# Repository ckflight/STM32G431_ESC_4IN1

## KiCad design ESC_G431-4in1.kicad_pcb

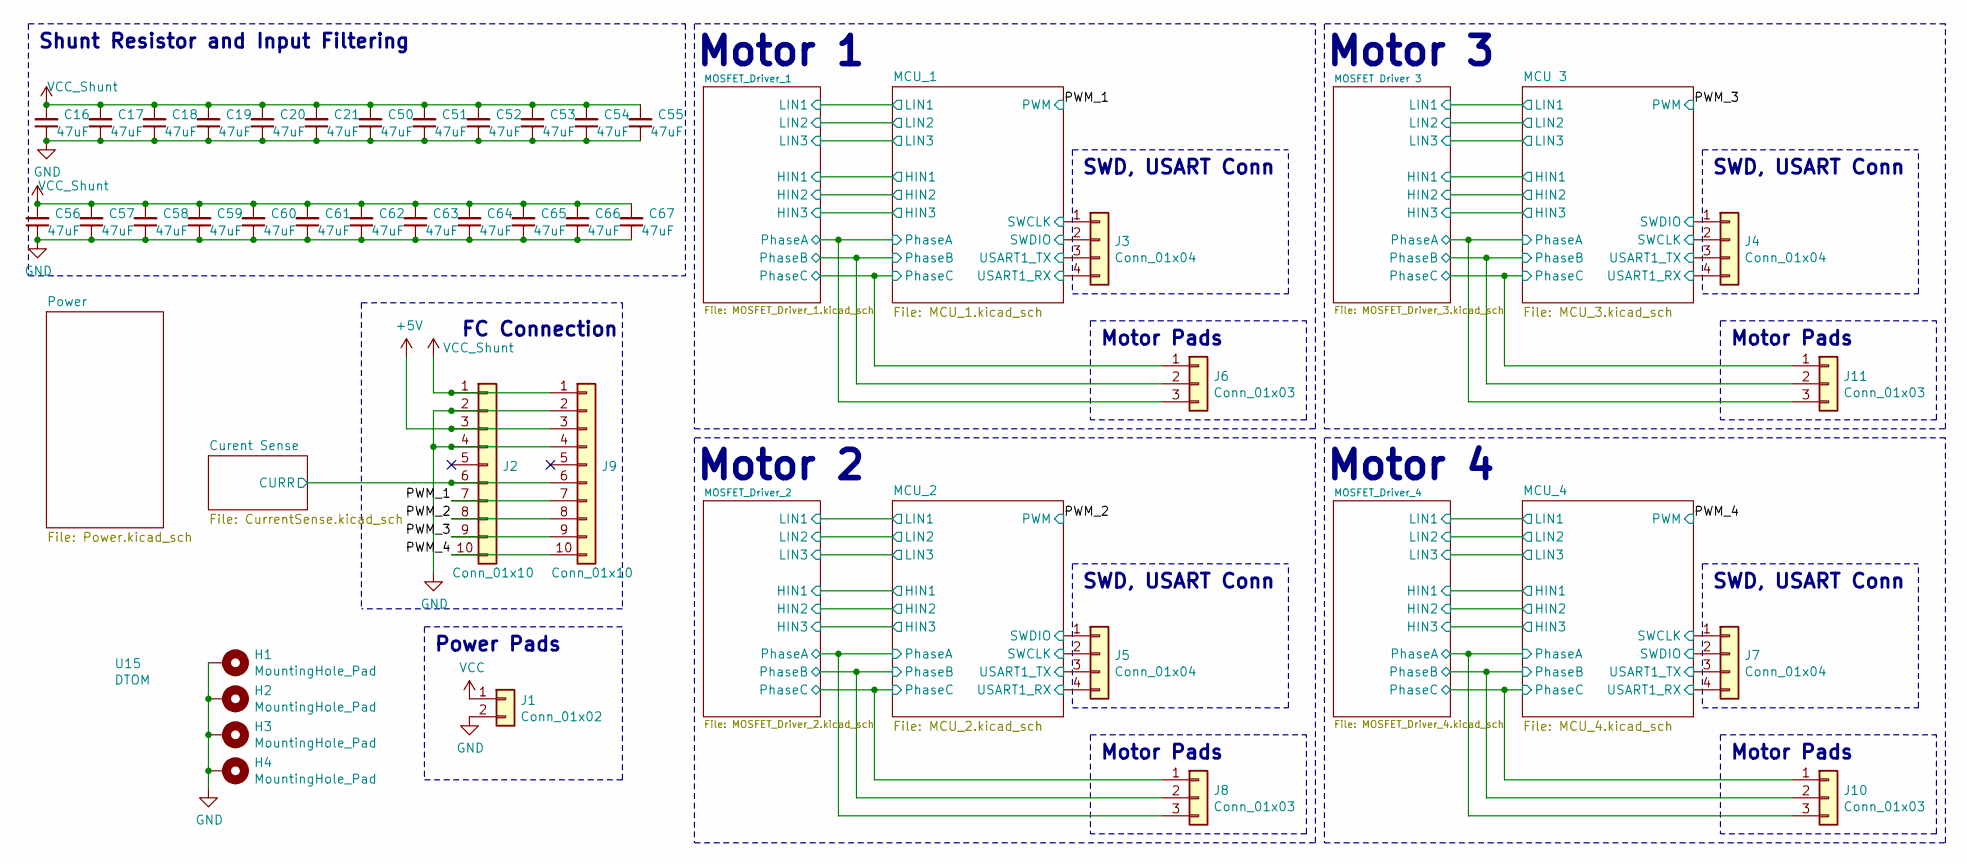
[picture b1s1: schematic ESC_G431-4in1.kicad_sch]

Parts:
C16, C17, C18, C19, C20, C21, C50, C51, C52, C53, C54, C55, C56, C57, C58, C59, C60, C61, C62, C63, C64, C65, C66, C67: 47uF; C_1206_3216Metric
H1, H2, H3, H4: MountingHole_Pad; MountingHole_4in1ESC
J1: Conn_01x02; Conn_PowerPad_4in1
J2: Conn_01x10; JST_SH_SM10B-SRSS-TB_1x10-1MP_P1.00mm_Horizontal
J3, J4, J5, J7: Conn_01x04; Conn_Debug
J6, J8, J10, J11: Conn_01x03; Conn_MotorPhase
J9: Conn_01x10; Conn_FC_Solder_10
U15: DTOM; DTOM_L

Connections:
+5V: J2.3, J9.3; also elsewhere on the board
/Curent Sense/CURR: J2.6, J9.6; also elsewhere on the board
/MCU 3/PhaseA: J11.3; also elsewhere on the board
/MCU 3/PhaseB: J11.2; also elsewhere on the board
/MCU 3/PhaseC: J11.1; also elsewhere on the board
/MCU 3/SWCLK: J4.2; also elsewhere on the board
/MCU 3/SWDIO: J4.1; also elsewhere on the board
/MCU 3/USART1_RX: J4.4; also elsewhere on the board
/MCU 3/USART1_TX: J4.3; also elsewhere on the board
/MCU_1/PhaseA: J6.3; also elsewhere on the board
/MCU_1/PhaseB: J6.2; also elsewhere on the board
/MCU_1/PhaseC: J6.1; also elsewhere on the board
/MCU_1/SWCLK: J3.1; also elsewhere on the board
/MCU_1/SWDIO: J3.2; also elsewhere on the board
/MCU_1/USART1_RX: J3.4; also elsewhere on the board
/MCU_1/USART1_TX: J3.3; also elsewhere on the board
/MCU_2/PhaseA: J8.3; also elsewhere on the board
/MCU_2/PhaseB: J8.2; also elsewhere on the board
/MCU_2/PhaseC: J8.1; also elsewhere on the board
/MCU_2/SWCLK: J5.2; also elsewhere on the board
/MCU_2/SWDIO: J5.1; also elsewhere on the board
/MCU_2/USART1_RX: J5.4; also elsewhere on the board
/MCU_2/USART1_TX: J5.3; also elsewhere on the board
/MCU_4/PhaseA: J10.3; also elsewhere on the board
/MCU_4/PhaseB: J10.2; also elsewhere on the board
/MCU_4/PhaseC: J10.1; also elsewhere on the board
/MCU_4/SWCLK: J7.1; also elsewhere on the board
/MCU_4/SWDIO: J7.2; also elsewhere on the board
/MCU_4/USART1_RX: J7.4; also elsewhere on the board
/MCU_4/USART1_TX: J7.3; also elsewhere on the board
/PWM_1: J2.7, J9.7; also elsewhere on the board
/PWM_2: J2.8, J9.8; also elsewhere on the board
/PWM_3: J2.9, J9.9; also elsewhere on the board
/PWM_4: J2.10, J9.10; also elsewhere on the board
GND: C16.1, C17.1, C18.1, C19.1, C20.1, C21.1, C50.1, C51.1, C52.1, C53.1, C54.1, C55.1, C56.1, C57.1, C58.1, C59.1, C60.1, C61.1, C62.1, C63.1, C64.1, C65.1, C66.1, C67.1, H1.1, H2.1, H3.1, H4.1, J1.2, J2.2, J2.4, J9.2, J9.4; also elsewhere on the board
VCC: J1.1; also elsewhere on the board
VCC_Shunt: C16.2, C17.2, C18.2, C19.2, C20.2, C21.2, C50.2, C51.2, C52.2, C53.2, C54.2, C55.2, C56.2, C57.2, C58.2, C59.2, C60.2, C61.2, C62.2, C63.2, C64.2, C65.2, C66.2, C67.2, J2.1, J9.1; also elsewhere on the board

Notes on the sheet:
SWD, USART Conn
Motor Pads
Motor 2
Motor 4
Motor 1
Motor 3
FC Connection
Shunt Resistor and Input Filtering
Power Pads

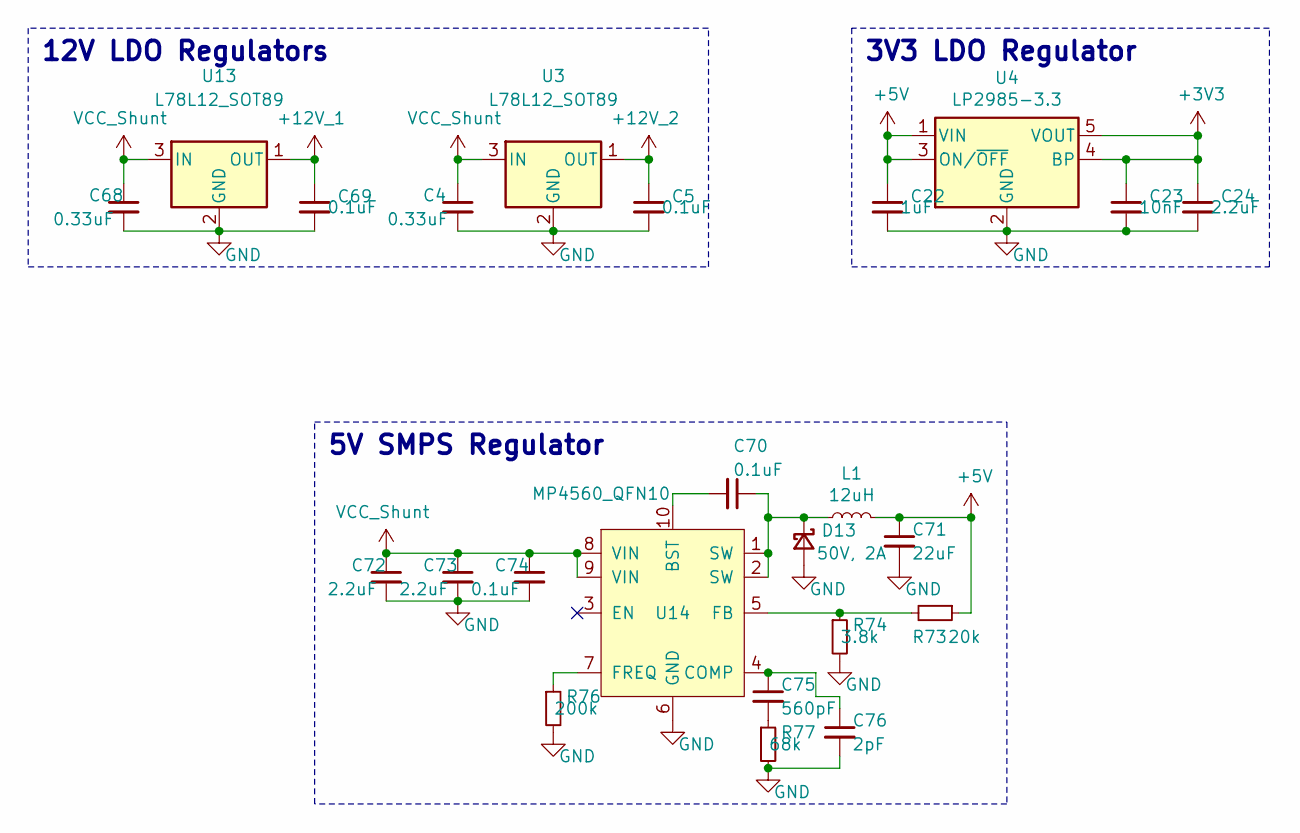
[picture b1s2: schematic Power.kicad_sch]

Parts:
C4, C68: 0.33uF; C_0603_1608Metric
C5, C69: 0.1uF; C_0603_1608Metric
C22: 1uF; C_0402_1005Metric
C23: 10nF; C_0402_1005Metric
C24, C72, C73: 2.2uF; C_0603_1608Metric
C70, C74: 0.1uF; C_0402_1005Metric
C71: 22uF; C_0603_1608Metric
C75: 560pF; C_0402_1005Metric
C76: 2pF; C_0402_1005Metric
D13: 50V, 2A; D_SOD-123F
L1: 12uH; L_XGL4030
R73: 20k; R_0402_1005Metric
R74: 3.8k; R_0402_1005Metric
R76: 200k; R_0402_1005Metric
R77: 68k; R_0402_1005Metric
U3, U13: L78L12_SOT89; L78L12ACUTR
U4: LP2985-3.3; SOT-23-5
U14: MP4560_QFN10; DFN-10-1EP_3x3mm_P0.5mm_EP1.7x2.5mm

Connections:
+3V3: C23.1, C24.1, U4.4 (BP), U4.5 (VOUT); also elsewhere on the board
+5V: C22.1, C71.1, L1.2, R73.1, U4.1 (VIN), U4.3 (ON/~OFF); also elsewhere on the board
+12V_1: C69.1, U13.1 (OUT); also elsewhere on the board
+12V_2: C5.1, U3.1 (OUT); also elsewhere on the board
GND: C4.2, C5.2, C22.2, C23.2, C24.2, C68.2, C69.2, C71.2, C72.2, C73.2, C74.2, C76.2, D13.2 (A), R74.2, R76.2, R77.2, U3.2 (GND), U4.2 (GND), U13.2 (GND), U14.6 (GND); also elsewhere on the board
unnamed: C70.1, D13.1 (K), L1.1, U14.1 (SW), U14.2 (SW)
unnamed: C70.2, U14.10 (BST)
unnamed: C75.1, C76.1, U14.4 (COMP)
unnamed: C75.2, R77.1
unnamed: R73.2, R74.1, U14.5 (FB)
unnamed: R76.1, U14.7 (FREQ)
VCC_Shunt: C4.1, C68.1, C72.1, C73.1, C74.1, U3.3 (IN), U13.3 (IN), U14.8 (VIN), U14.9 (VIN); also elsewhere on the board

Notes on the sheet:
12V LDO Regulators
3V3 LDO Regulator
5V SMPS Regulator

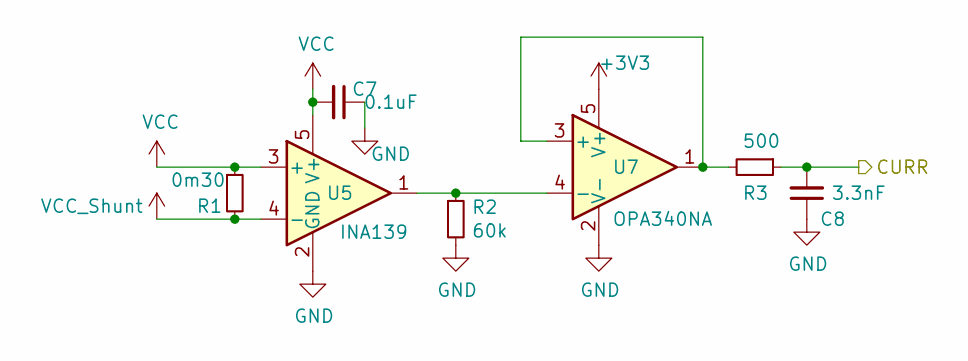
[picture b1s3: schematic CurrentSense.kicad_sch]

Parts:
C7: 0.1uF; C_0402_1005Metric
C8: 3.3nF; C_0402_1005Metric
R1: 0m30; R_Shunt_Vishay_WSLP2726
R2: 60k; R_0402_1005Metric
R3: 500; R_0402_1005Metric
U5: INA139; SOT-23-5
U7: OPA340NA; SOT-23-5

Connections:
+3V3: U7.5 (V+); also elsewhere on the board
/Curent Sense/CURR: C8.2, R3.1; also elsewhere on the board
GND: C7.1, C8.1, R2.2, U5.2 (GND), U7.2 (V-); also elsewhere on the board
unnamed: R2.1, U5.1, U7.4 (-)
unnamed: R3.2, U7.1, U7.3 (+)
VCC: C7.2, R1.1, U5.3 (+), U5.5 (V+); also elsewhere on the board
VCC_Shunt: R1.2, U5.4 (-); also elsewhere on the board

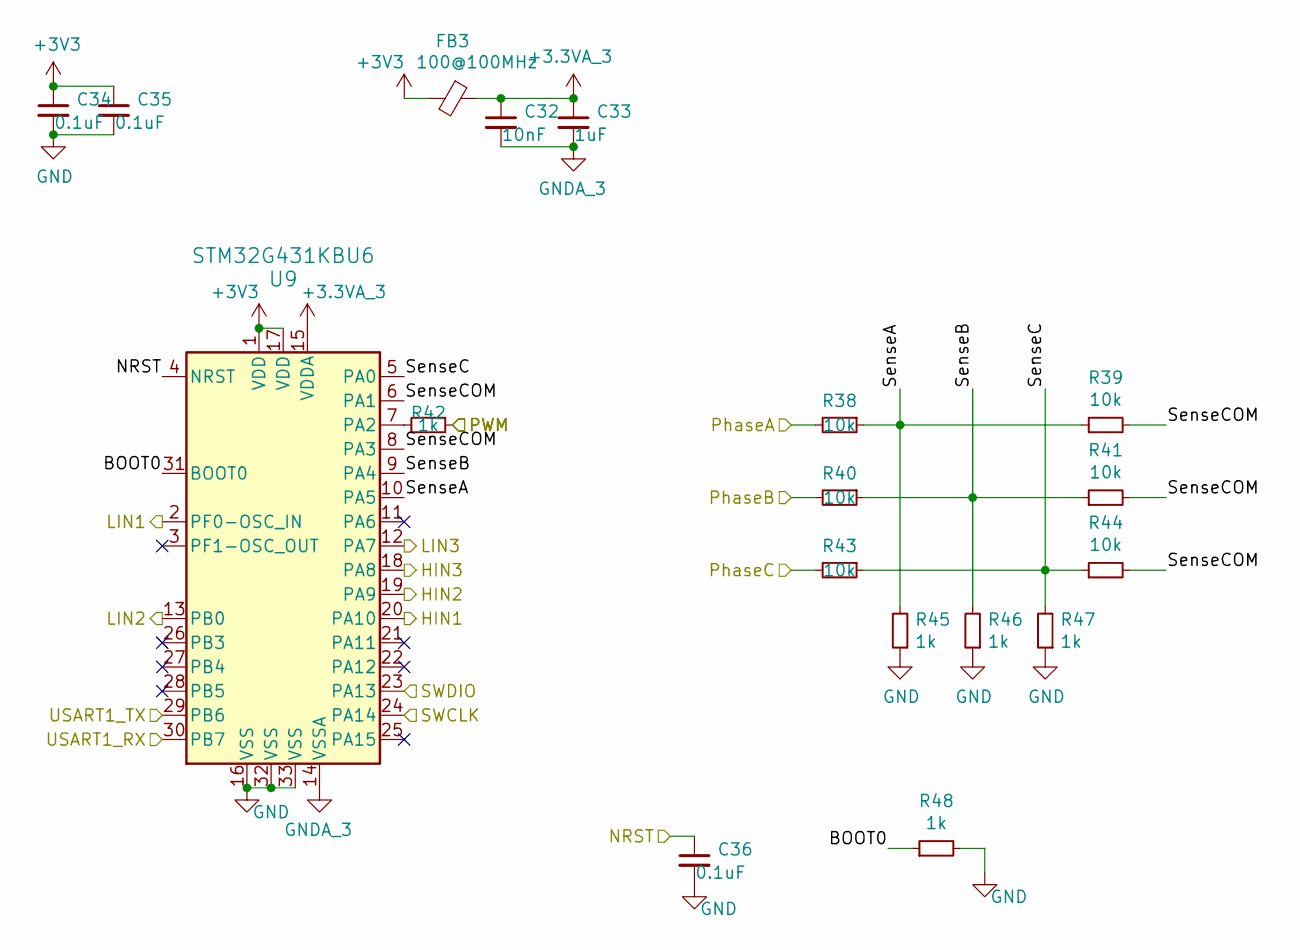
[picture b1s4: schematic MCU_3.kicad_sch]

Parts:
C32: 10nF; C_0402_1005Metric
C33: 1uF; C_0402_1005Metric
C34, C35, C36: 0.1uF; C_0402_1005Metric
FB3: 100@100MHz; L_0603_1608Metric
R38, R39, R40, R41, R43, R44: 10k; R_0402_1005Metric
R42, R45, R46, R47, R48: 1k; R_0402_1005Metric
U9: STM32G431KBU6; QFN-32-1EP_5x5mm_P0.5mm_EP3.45x3.45mm_STM32

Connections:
+3.3VA_3: C32.1, C33.1, FB3.1, U9.15 (VDDA)
+3V3: C34.1, C35.1, FB3.2, U9.1 (VDD), U9.17 (VDD); also elsewhere on the board
/MCU 3/BOOT0: R48.1, U9.31 (BOOT0)
/MCU 3/HIN1: U9.20 (PA10); also elsewhere on the board
/MCU 3/HIN2: U9.19 (PA9); also elsewhere on the board
/MCU 3/HIN3: U9.18 (PA8); also elsewhere on the board
/MCU 3/LIN1: U9.2 (PF0-OSC_IN); also elsewhere on the board
/MCU 3/LIN2: U9.13 (PB0); also elsewhere on the board
/MCU 3/LIN3: U9.12 (PA7); also elsewhere on the board
/MCU 3/NRST: C36.1, U9.4 (NRST)
/MCU 3/PhaseA: R38.2; also elsewhere on the board
/MCU 3/PhaseB: R40.2; also elsewhere on the board
/MCU 3/PhaseC: R43.2; also elsewhere on the board
/MCU 3/SWCLK: U9.24 (PA14); also elsewhere on the board
/MCU 3/SWDIO: U9.23 (PA13); also elsewhere on the board
/MCU 3/SenseA: R38.1, R39.1, R45.2, U9.10 (PA5)
/MCU 3/SenseB: R40.1, R41.1, R46.2, U9.9 (PA4)
/MCU 3/SenseC: R43.1, R44.1, R47.2, U9.5 (PA0)
/MCU 3/SenseCOM: R39.2, R41.2, R44.2, U9.6 (PA1), U9.8 (PA3)
/MCU 3/USART1_RX: U9.30 (PB7); also elsewhere on the board
/MCU 3/USART1_TX: U9.29 (PB6); also elsewhere on the board
/PWM_3: R42.2; also elsewhere on the board
GND: C34.2, C35.2, C36.2, R45.1, R46.1, R47.1, R48.2, U9.16 (VSS), U9.32 (VSS), U9.33 (VSS); also elsewhere on the board
GNDA_3: C32.2, C33.2, U9.14 (VSSA)
unnamed: R42.1, U9.7 (PA2)

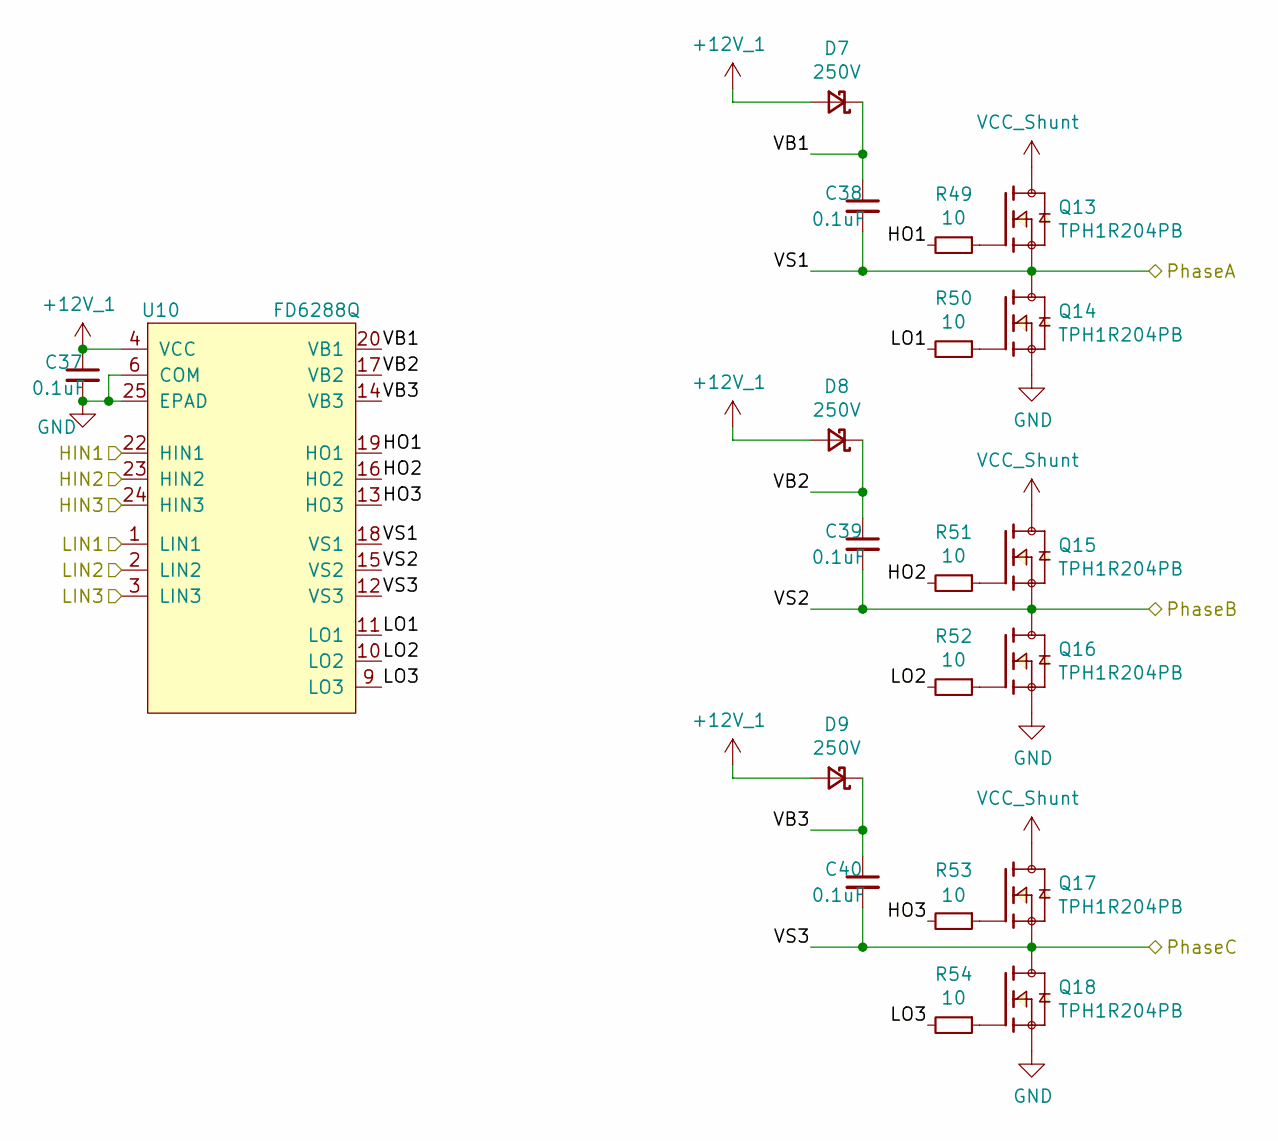
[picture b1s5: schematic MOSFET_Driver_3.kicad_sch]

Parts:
C37: 0.1uF; C_0402_1005Metric
C38, C39, C40: 0.1uF; C_0603_1608Metric
D7, D8, D9: 250V; D_SOD-523
Q13, Q14, Q15, Q16, Q17, Q18: TPH1R204PB; PARTREV 3
R49, R50, R51, R52, R53, R54: 10; R_0402_1005Metric
U10: FD6288Q; QFN-24-1EP_4x4mm_P0.5mm_EP2.7x2.7mm

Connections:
+12V_1: C37.1, D7.2 (A), D8.2 (A), D9.2 (A), U10.4 (VCC); also elsewhere on the board
/MCU 3/HIN1: U10.22 (HIN1); also elsewhere on the board
/MCU 3/HIN2: U10.23 (HIN2); also elsewhere on the board
/MCU 3/HIN3: U10.24 (HIN3); also elsewhere on the board
/MCU 3/LIN1: U10.1 (LIN1); also elsewhere on the board
/MCU 3/LIN2: U10.2 (LIN2); also elsewhere on the board
/MCU 3/LIN3: U10.3 (LIN3); also elsewhere on the board
/MCU 3/PhaseA: C38.2, Q13.1, Q13.2, Q13.3, Q14.5, Q14.6, Q14.7, Q14.8, Q14.9, U10.18 (VS1); also elsewhere on the board
/MCU 3/PhaseB: C39.2, Q15.1, Q15.2, Q15.3, Q16.5, Q16.6, Q16.7, Q16.8, Q16.9, U10.15 (VS2); also elsewhere on the board
/MCU 3/PhaseC: C40.2, Q17.1, Q17.2, Q17.3, Q18.5, Q18.6, Q18.7, Q18.8, Q18.9, U10.12 (VS3); also elsewhere on the board
/MOSFET Driver 3/HO1: R49.2, U10.19 (HO1)
/MOSFET Driver 3/HO2: R51.2, U10.16 (HO2)
/MOSFET Driver 3/HO3: R53.2, U10.13 (HO3)
/MOSFET Driver 3/LO1: R50.2, U10.11 (LO1)
/MOSFET Driver 3/LO2: R52.2, U10.10 (LO2)
/MOSFET Driver 3/LO3: R54.2, U10.9 (LO3)
/MOSFET Driver 3/VB1: C38.1, D7.1 (K), U10.20 (VB1)
/MOSFET Driver 3/VB2: C39.1, D8.1 (K), U10.17 (VB2)
/MOSFET Driver 3/VB3: C40.1, D9.1 (K), U10.14 (VB3)
GND: C37.2, Q14.1, Q14.2, Q14.3, Q16.1, Q16.2, Q16.3, Q18.1, Q18.2, Q18.3, U10.6 (COM), U10.25 (EPAD); also elsewhere on the board
unnamed: Q13.4, R49.1
unnamed: Q14.4, R50.1
unnamed: Q15.4, R51.1
unnamed: Q16.4, R52.1
unnamed: Q17.4, R53.1
unnamed: Q18.4, R54.1
VCC_Shunt: Q13.5, Q13.6, Q13.7, Q13.8, Q13.9, Q15.5, Q15.6, Q15.7, Q15.8, Q15.9, Q17.5, Q17.6, Q17.7, Q17.8, Q17.9; also elsewhere on the board

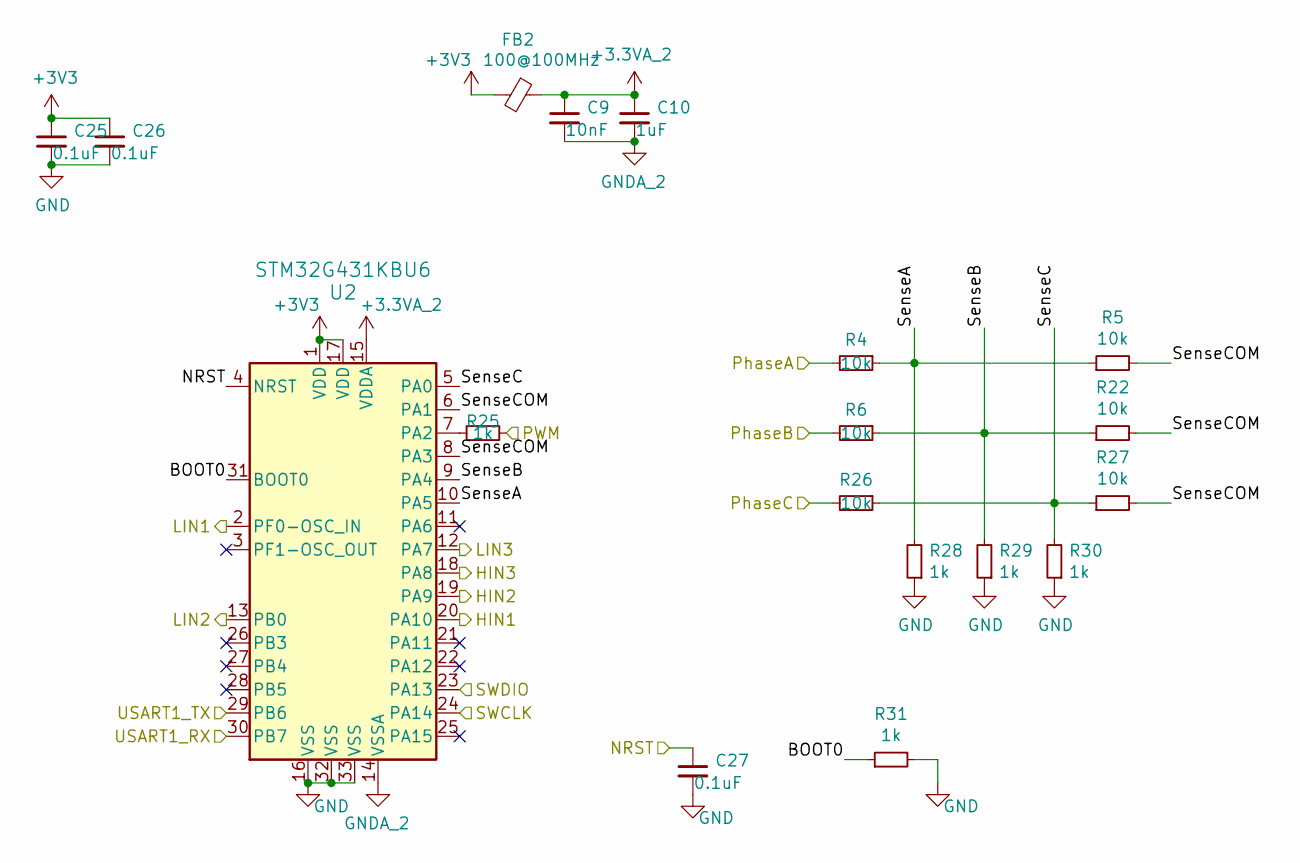
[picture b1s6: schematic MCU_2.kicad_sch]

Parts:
C9: 10nF; C_0402_1005Metric
C10: 1uF; C_0402_1005Metric
C25, C26, C27: 0.1uF; C_0402_1005Metric
FB2: 100@100MHz; L_0603_1608Metric
R4, R5, R6, R22, R26, R27: 10k; R_0402_1005Metric
R25, R28, R29, R30, R31: 1k; R_0402_1005Metric
U2: STM32G431KBU6; QFN-32-1EP_5x5mm_P0.5mm_EP3.45x3.45mm_STM32

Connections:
+3.3VA_2: C9.1, C10.1, FB2.1, U2.15 (VDDA)
+3V3: C25.1, C26.1, FB2.2, U2.1 (VDD), U2.17 (VDD); also elsewhere on the board
/MCU_2/BOOT0: R31.1, U2.31 (BOOT0)
/MCU_2/HIN1: U2.20 (PA10); also elsewhere on the board
/MCU_2/HIN2: U2.19 (PA9); also elsewhere on the board
/MCU_2/HIN3: U2.18 (PA8); also elsewhere on the board
/MCU_2/LIN1: U2.2 (PF0-OSC_IN); also elsewhere on the board
/MCU_2/LIN2: U2.13 (PB0); also elsewhere on the board
/MCU_2/LIN3: U2.12 (PA7); also elsewhere on the board
/MCU_2/NRST: C27.1, U2.4 (NRST)
/MCU_2/PhaseA: R4.2; also elsewhere on the board
/MCU_2/PhaseB: R6.2; also elsewhere on the board
/MCU_2/PhaseC: R26.2; also elsewhere on the board
/MCU_2/SWCLK: U2.24 (PA14); also elsewhere on the board
/MCU_2/SWDIO: U2.23 (PA13); also elsewhere on the board
/MCU_2/SenseA: R4.1, R5.1, R28.2, U2.10 (PA5)
/MCU_2/SenseB: R6.1, R22.1, R29.2, U2.9 (PA4)
/MCU_2/SenseC: R26.1, R27.1, R30.2, U2.5 (PA0)
/MCU_2/SenseCOM: R5.2, R22.2, R27.2, U2.6 (PA1), U2.8 (PA3)
/MCU_2/USART1_RX: U2.30 (PB7); also elsewhere on the board
/MCU_2/USART1_TX: U2.29 (PB6); also elsewhere on the board
/PWM_2: R25.2; also elsewhere on the board
GND: C25.2, C26.2, C27.2, R28.1, R29.1, R30.1, R31.2, U2.16 (VSS), U2.32 (VSS), U2.33 (VSS); also elsewhere on the board
GNDA_2: C9.2, C10.2, U2.14 (VSSA)
unnamed: R25.1, U2.7 (PA2)

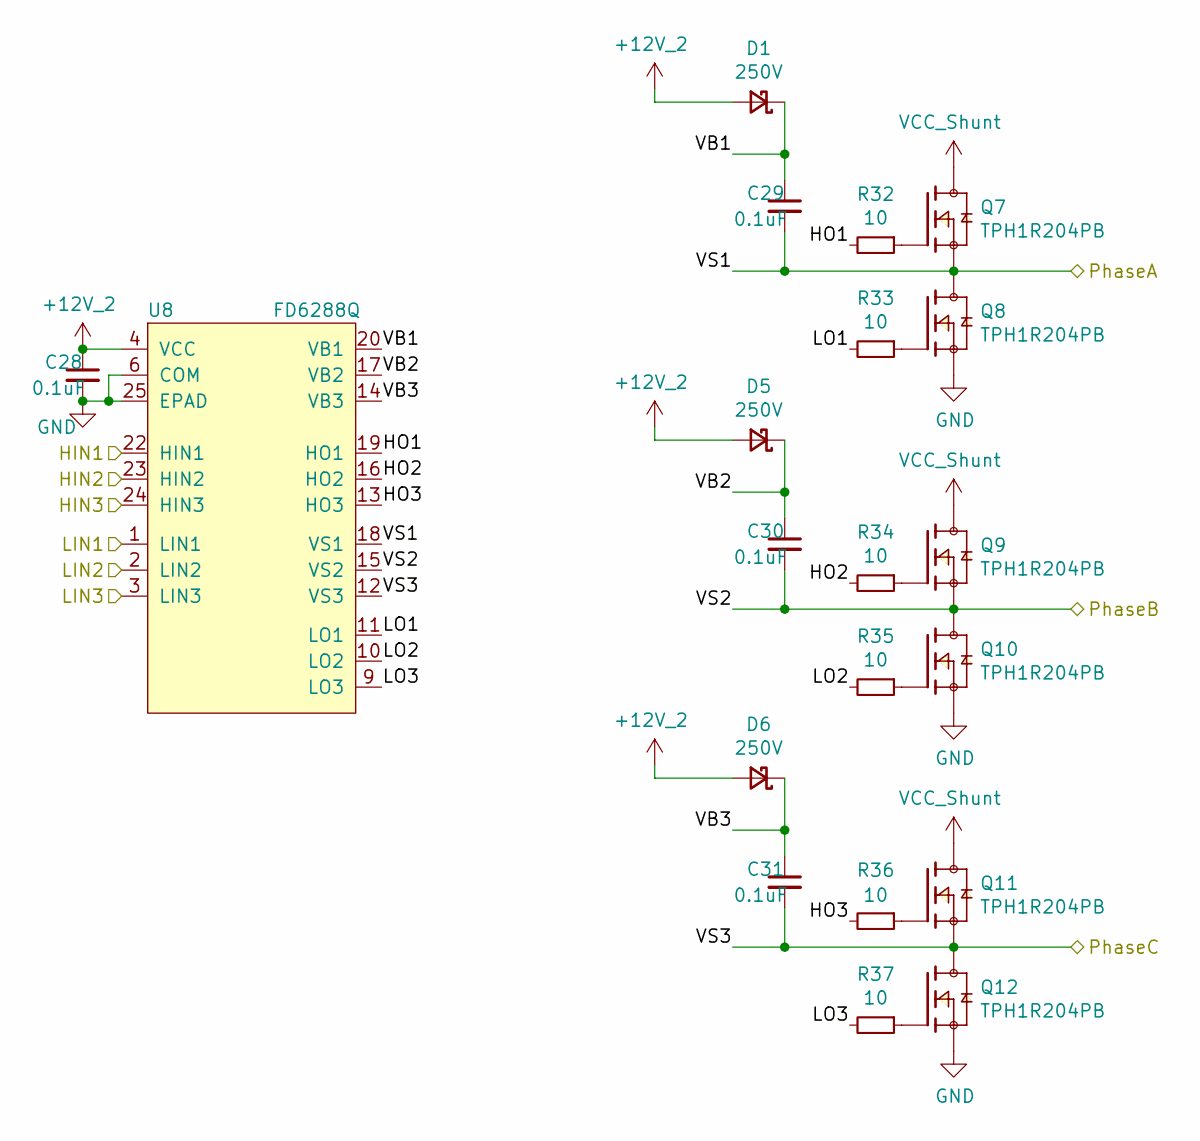
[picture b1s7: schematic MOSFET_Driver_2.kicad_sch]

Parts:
C28: 0.1uF; C_0402_1005Metric
C29, C30, C31: 0.1uF; C_0603_1608Metric
D1, D5, D6: 250V; D_SOD-523
Q7, Q8, Q9, Q10, Q11, Q12: TPH1R204PB; PARTREV 3
R32, R33, R34, R35, R36, R37: 10; R_0402_1005Metric
U8: FD6288Q; QFN-24-1EP_4x4mm_P0.5mm_EP2.7x2.7mm

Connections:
+12V_2: C28.1, D1.2 (A), D5.2 (A), D6.2 (A), U8.4 (VCC); also elsewhere on the board
/MCU_2/HIN1: U8.22 (HIN1); also elsewhere on the board
/MCU_2/HIN2: U8.23 (HIN2); also elsewhere on the board
/MCU_2/HIN3: U8.24 (HIN3); also elsewhere on the board
/MCU_2/LIN1: U8.1 (LIN1); also elsewhere on the board
/MCU_2/LIN2: U8.2 (LIN2); also elsewhere on the board
/MCU_2/LIN3: U8.3 (LIN3); also elsewhere on the board
/MCU_2/PhaseA: C29.2, Q7.1, Q7.2, Q7.3, Q8.5, Q8.6, Q8.7, Q8.8, Q8.9, U8.18 (VS1); also elsewhere on the board
/MCU_2/PhaseB: C30.2, Q9.1, Q9.2, Q9.3, Q10.5, Q10.6, Q10.7, Q10.8, Q10.9, U8.15 (VS2); also elsewhere on the board
/MCU_2/PhaseC: C31.2, Q11.1, Q11.2, Q11.3, Q12.5, Q12.6, Q12.7, Q12.8, Q12.9, U8.12 (VS3); also elsewhere on the board
/MOSFET_Driver_2/HO1: R32.2, U8.19 (HO1)
/MOSFET_Driver_2/HO2: R34.2, U8.16 (HO2)
/MOSFET_Driver_2/HO3: R36.2, U8.13 (HO3)
/MOSFET_Driver_2/LO1: R33.2, U8.11 (LO1)
/MOSFET_Driver_2/LO2: R35.2, U8.10 (LO2)
/MOSFET_Driver_2/LO3: R37.2, U8.9 (LO3)
/MOSFET_Driver_2/VB1: C29.1, D1.1 (K), U8.20 (VB1)
/MOSFET_Driver_2/VB2: C30.1, D5.1 (K), U8.17 (VB2)
/MOSFET_Driver_2/VB3: C31.1, D6.1 (K), U8.14 (VB3)
GND: C28.2, Q8.1, Q8.2, Q8.3, Q10.1, Q10.2, Q10.3, Q12.1, Q12.2, Q12.3, U8.6 (COM), U8.25 (EPAD); also elsewhere on the board
unnamed: Q7.4, R32.1
unnamed: Q8.4, R33.1
unnamed: Q9.4, R34.1
unnamed: Q10.4, R35.1
unnamed: Q11.4, R36.1
unnamed: Q12.4, R37.1
VCC_Shunt: Q7.5, Q7.6, Q7.7, Q7.8, Q7.9, Q9.5, Q9.6, Q9.7, Q9.8, Q9.9, Q11.5, Q11.6, Q11.7, Q11.8, Q11.9; also elsewhere on the board

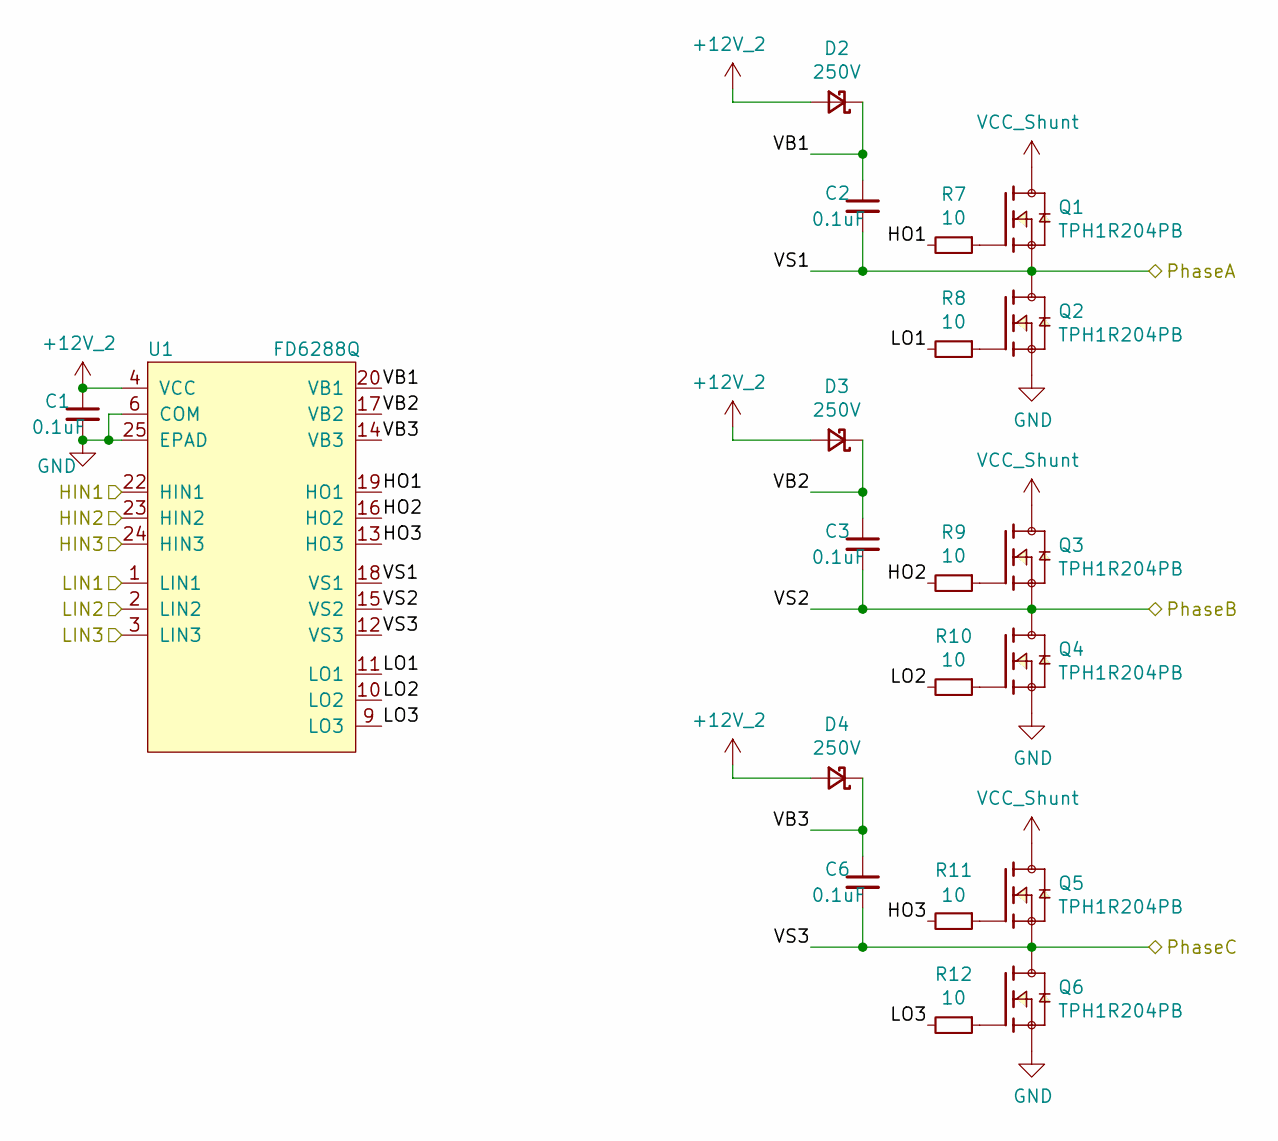
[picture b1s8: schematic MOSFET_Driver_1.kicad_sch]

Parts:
C1: 0.1uF; C_0402_1005Metric
C2, C3, C6: 0.1uF; C_0603_1608Metric
D2, D3, D4: 250V; D_SOD-523
Q1, Q2, Q3, Q4, Q5, Q6: TPH1R204PB; PARTREV 3
R7, R8, R9, R10, R11, R12: 10; R_0402_1005Metric
U1: FD6288Q; QFN-24-1EP_4x4mm_P0.5mm_EP2.7x2.7mm

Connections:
+12V_2: C1.1, D2.2 (A), D3.2 (A), D4.2 (A), U1.4 (VCC); also elsewhere on the board
/MCU_1/HIN1: U1.22 (HIN1); also elsewhere on the board
/MCU_1/HIN2: U1.23 (HIN2); also elsewhere on the board
/MCU_1/HIN3: U1.24 (HIN3); also elsewhere on the board
/MCU_1/LIN1: U1.1 (LIN1); also elsewhere on the board
/MCU_1/LIN2: U1.2 (LIN2); also elsewhere on the board
/MCU_1/LIN3: U1.3 (LIN3); also elsewhere on the board
/MCU_1/PhaseA: C2.2, Q1.1, Q1.2, Q1.3, Q2.5, Q2.6, Q2.7, Q2.8, Q2.9, U1.18 (VS1); also elsewhere on the board
/MCU_1/PhaseB: C3.2, Q3.1, Q3.2, Q3.3, Q4.5, Q4.6, Q4.7, Q4.8, Q4.9, U1.15 (VS2); also elsewhere on the board
/MCU_1/PhaseC: C6.2, Q5.1, Q5.2, Q5.3, Q6.5, Q6.6, Q6.7, Q6.8, Q6.9, U1.12 (VS3); also elsewhere on the board
/MOSFET_Driver_1/HO1: R7.2, U1.19 (HO1)
/MOSFET_Driver_1/HO2: R9.2, U1.16 (HO2)
/MOSFET_Driver_1/HO3: R11.2, U1.13 (HO3)
/MOSFET_Driver_1/LO1: R8.2, U1.11 (LO1)
/MOSFET_Driver_1/LO2: R10.2, U1.10 (LO2)
/MOSFET_Driver_1/LO3: R12.2, U1.9 (LO3)
/MOSFET_Driver_1/VB1: C2.1, D2.1 (K), U1.20 (VB1)
/MOSFET_Driver_1/VB2: C3.1, D3.1 (K), U1.17 (VB2)
/MOSFET_Driver_1/VB3: C6.1, D4.1 (K), U1.14 (VB3)
GND: C1.2, Q2.1, Q2.2, Q2.3, Q4.1, Q4.2, Q4.3, Q6.1, Q6.2, Q6.3, U1.6 (COM), U1.25 (EPAD); also elsewhere on the board
unnamed: Q1.4, R7.1
unnamed: Q2.4, R8.1
unnamed: Q3.4, R9.1
unnamed: Q4.4, R10.1
unnamed: Q5.4, R11.1
unnamed: Q6.4, R12.1
VCC_Shunt: Q1.5, Q1.6, Q1.7, Q1.8, Q1.9, Q3.5, Q3.6, Q3.7, Q3.8, Q3.9, Q5.5, Q5.6, Q5.7, Q5.8, Q5.9; also elsewhere on the board

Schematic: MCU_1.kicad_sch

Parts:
C11: 10nF; C_0402_1005Metric
C12: 1uF; C_0402_1005Metric
C13, C14, C15: 0.1uF; C_0402_1005Metric
FB1: 100@100MHz; L_0603_1608Metric
R13, R14, R16, R17, R18, R19: 10k; R_0402_1005Metric
R15, R20, R21, R23, R24: 1k; R_0402_1005Metric
U6: STM32G431KBU6; QFN-32-1EP_5x5mm_P0.5mm_EP3.45x3.45mm_STM32

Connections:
+3.3VA_1: C11.1, C12.1, FB1.1, U6.15 (VDDA)
+3V3: C13.1, C14.1, FB1.2, U6.1 (VDD), U6.17 (VDD); also elsewhere on the board
/MCU_1/BOOT0: R24.1, U6.31 (BOOT0)
/MCU_1/HIN1: U6.20 (PA10); also elsewhere on the board
/MCU_1/HIN2: U6.19 (PA9); also elsewhere on the board
/MCU_1/HIN3: U6.18 (PA8); also elsewhere on the board
/MCU_1/LIN1: U6.2 (PF0-OSC_IN); also elsewhere on the board
/MCU_1/LIN2: U6.13 (PB0); also elsewhere on the board
/MCU_1/LIN3: U6.12 (PA7); also elsewhere on the board
/MCU_1/NRST: C15.1, U6.4 (NRST)
/MCU_1/PhaseA: R13.2; also elsewhere on the board
/MCU_1/PhaseB: R16.2; also elsewhere on the board
/MCU_1/PhaseC: R18.2; also elsewhere on the board
/MCU_1/SWCLK: U6.24 (PA14); also elsewhere on the board
/MCU_1/SWDIO: U6.23 (PA13); also elsewhere on the board
/MCU_1/SenseA: R13.1, R14.1, R20.2, U6.10 (PA5)
/MCU_1/SenseB: R16.1, R17.1, R21.2, U6.9 (PA4)
/MCU_1/SenseC: R18.1, R19.1, R23.2, U6.5 (PA0)
/MCU_1/SenseCOM: R14.2, R17.2, R19.2, U6.6 (PA1), U6.8 (PA3)
/MCU_1/USART1_RX: U6.30 (PB7); also elsewhere on the board
/MCU_1/USART1_TX: U6.29 (PB6); also elsewhere on the board
/PWM_1: R15.2; also elsewhere on the board
GND: C13.2, C14.2, C15.2, R20.1, R21.1, R23.1, R24.2, U6.16 (VSS), U6.32 (VSS), U6.33 (VSS); also elsewhere on the board
GNDA_1: C11.2, C12.2, U6.14 (VSSA)
unnamed: R15.1, U6.7 (PA2)

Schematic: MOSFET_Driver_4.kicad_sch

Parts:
C41: 0.1uF; C_0402_1005Metric
C42, C43, C44: 0.1uF; C_0603_1608Metric
D10, D11, D12: 250V; D_SOD-523
Q19, Q20, Q21, Q22, Q23, Q24: TPH1R204PB; PARTREV 3
R55, R56, R57, R58, R59, R60: 10; R_0402_1005Metric
U11: FD6288Q; QFN-24-1EP_4x4mm_P0.5mm_EP2.7x2.7mm

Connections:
+12V_1: C41.1, D10.2 (A), D11.2 (A), D12.2 (A), U11.4 (VCC); also elsewhere on the board
/MCU_4/HIN1: U11.22 (HIN1); also elsewhere on the board
/MCU_4/HIN2: U11.23 (HIN2); also elsewhere on the board
/MCU_4/HIN3: U11.24 (HIN3); also elsewhere on the board
/MCU_4/LIN1: U11.1 (LIN1); also elsewhere on the board
/MCU_4/LIN2: U11.2 (LIN2); also elsewhere on the board
/MCU_4/LIN3: U11.3 (LIN3); also elsewhere on the board
/MCU_4/PhaseA: C42.2, Q19.1, Q19.2, Q19.3, Q20.5, Q20.6, Q20.7, Q20.8, Q20.9, U11.18 (VS1); also elsewhere on the board
/MCU_4/PhaseB: C43.2, Q21.1, Q21.2, Q21.3, Q22.5, Q22.6, Q22.7, Q22.8, Q22.9, U11.15 (VS2); also elsewhere on the board
/MCU_4/PhaseC: C44.2, Q23.1, Q23.2, Q23.3, Q24.5, Q24.6, Q24.7, Q24.8, Q24.9, U11.12 (VS3); also elsewhere on the board
/MOSFET_Driver_4/HO1: R55.2, U11.19 (HO1)
/MOSFET_Driver_4/HO2: R57.2, U11.16 (HO2)
/MOSFET_Driver_4/HO3: R59.2, U11.13 (HO3)
/MOSFET_Driver_4/LO1: R56.2, U11.11 (LO1)
/MOSFET_Driver_4/LO2: R58.2, U11.10 (LO2)
/MOSFET_Driver_4/LO3: R60.2, U11.9 (LO3)
/MOSFET_Driver_4/VB1: C42.1, D10.1 (K), U11.20 (VB1)
/MOSFET_Driver_4/VB2: C43.1, D11.1 (K), U11.17 (VB2)
/MOSFET_Driver_4/VB3: C44.1, D12.1 (K), U11.14 (VB3)
GND: C41.2, Q20.1, Q20.2, Q20.3, Q22.1, Q22.2, Q22.3, Q24.1, Q24.2, Q24.3, U11.6 (COM), U11.25 (EPAD); also elsewhere on the board
unnamed: Q19.4, R55.1
unnamed: Q20.4, R56.1
unnamed: Q21.4, R57.1
unnamed: Q22.4, R58.1
unnamed: Q23.4, R59.1
unnamed: Q24.4, R60.1
VCC_Shunt: Q19.5, Q19.6, Q19.7, Q19.8, Q19.9, Q21.5, Q21.6, Q21.7, Q21.8, Q21.9, Q23.5, Q23.6, Q23.7, Q23.8, Q23.9; also elsewhere on the board

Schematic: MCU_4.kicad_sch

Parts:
C45: 10nF; C_0402_1005Metric
C46: 1uF; C_0402_1005Metric
C47, C48, C49: 0.1uF; C_0402_1005Metric
FB4: 100@100MHz; L_0603_1608Metric
R61, R62, R63, R64, R66, R67: 10k; R_0402_1005Metric
R65, R68, R69, R70, R71: 1k; R_0402_1005Metric
U12: STM32G431KBU6; QFN-32-1EP_5x5mm_P0.5mm_EP3.45x3.45mm_STM32

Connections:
+3.3VA_4: C45.1, C46.1, FB4.1, U12.15 (VDDA)
+3V3: C47.1, C48.1, FB4.2, U12.1 (VDD), U12.17 (VDD); also elsewhere on the board
/MCU_4/BOOT0: R71.1, U12.31 (BOOT0)
/MCU_4/HIN1: U12.20 (PA10); also elsewhere on the board
/MCU_4/HIN2: U12.19 (PA9); also elsewhere on the board
/MCU_4/HIN3: U12.18 (PA8); also elsewhere on the board
/MCU_4/LIN1: U12.2 (PF0-OSC_IN); also elsewhere on the board
/MCU_4/LIN2: U12.13 (PB0); also elsewhere on the board
/MCU_4/LIN3: U12.12 (PA7); also elsewhere on the board
/MCU_4/NRST: C49.1, U12.4 (NRST)
/MCU_4/PhaseA: R61.2; also elsewhere on the board
/MCU_4/PhaseB: R63.2; also elsewhere on the board
/MCU_4/PhaseC: R66.2; also elsewhere on the board
/MCU_4/SWCLK: U12.24 (PA14); also elsewhere on the board
/MCU_4/SWDIO: U12.23 (PA13); also elsewhere on the board
/MCU_4/SenseA: R61.1, R62.1, R68.2, U12.10 (PA5)
/MCU_4/SenseB: R63.1, R64.1, R69.2, U12.9 (PA4)
/MCU_4/SenseC: R66.1, R67.1, R70.2, U12.5 (PA0)
/MCU_4/SenseCOM: R62.2, R64.2, R67.2, U12.6 (PA1), U12.8 (PA3)
/MCU_4/USART1_RX: U12.30 (PB7); also elsewhere on the board
/MCU_4/USART1_TX: U12.29 (PB6); also elsewhere on the board
/PWM_4: R65.2; also elsewhere on the board
GND: C47.2, C48.2, C49.2, R68.1, R69.1, R70.1, R71.2, U12.16 (VSS), U12.32 (VSS), U12.33 (VSS); also elsewhere on the board
GNDA_4: C45.2, C46.2, U12.14 (VSSA)
unnamed: R65.1, U12.7 (PA2)

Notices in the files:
parts and their libraries:
Copyright 2016 Accelerated Designs. All rights reserved.
